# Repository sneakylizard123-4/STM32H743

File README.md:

# STM32H743 FPGA Devboard

> A STM32H743 board with an iCE40 UP5K FPGA, USB High-Speed PHY, Ethernet, and audio I/O.

This board puts an STM32H743XIH6 and an iCE40 UP5K on the same PCB.
The H743 handles control, USB, Ethernet, storage, and audio.
The UP5K provides small programmable logic for custom interfaces and filters, and also an easy way to goof off with the FPGA.
The design is aimed at audio DSP and FPGA experiments that would otherwise need several dev boards.

## Project Status

The board has not been fabricated, assembled, or brought up yet.
Bare-metal firmware is included and builds cleanly, but it has not been run on hardware.
An enclosure and a full mechanical assembly are not included in this revision.

## Custom Features

- STM32H743XIH6, with 2 MB flash and external memory buses exposed on headers.
- iCE40 UP5K FPGA connected to the MCU and to two 2.54 mm headers for logic experiments.
- USB3300 ULPI PHY for USB 2.0 High-Speed, with ESD protection.
- LAN8742A 10/100 Ethernet PHY and an RJ45 jack with integrated magnetics.
- Si5351C clock generator with a 25 MHz TCXO and a 25 MHz crystal. A 32.768 kHz crystal feeds the RTC/LSE on the STM32.
- CS4344 stereo I2S DAC, a 3.5 mm output jack, and two microphones (ICS-43434 and MMICT390200012).
- MicroSD socket on a 4-bit SDMMC bus.
- USB-C sink port for power and USB-A host port with a 500mA power switch.
- Four LDO rails (3.3 V, 2.5 V, 1.8 V, 1.2 V) with ferrite-filtered FPGA supplies.

## How It Works

| Block | Part | Role |
|-------|------|------|
| MCU | STM32H743XIH6 | Main controller, USB, Ethernet MAC, SDMMC, audio, control |
| FPGA | ICE40UP5K-SG48I | Programmable logic and custom interfaces |
| USB PHY | USB3300-EZK | ULPI PHY for USB 2.0 High-Speed |
| Ethernet PHY | LAN8742A | RMII 10/100 PHY |
| Clock | Si5351C-B-GM | Eight-output clock generator |
| Audio DAC | CS4344 | Stereo I2S DAC to the 3.5 mm jack |
| Microphones | ICS-43434, MMICT390200012 | PDM digital microphones |
| Storage | Hirose DM3D-SF | microSD card socket on SDMMC |
| USB power | TPD3S014 | Current-limited USB-A host port switch |
| Power | TLV75733, TLV75725, TLV75718, TLV75712 | 3.3 V, 2.5 V, 1.8 V, and 1.2 V LDO rails |

### Power Tree

```mermaid
flowchart LR
  USB["USB 5 V VBUS"] --> LDO33["U4 TLV75733 3.3 V"]
  USB --> LDO25["U5 TLV75725 2.5 V"]
  USB --> LDO18["U6 TLV75718 1.8 V"]
  USB --> LDO12["U7 TLV75712 1.2 V"]
  LDO33 --> MCU["STM32H743, PHYs, SD, audio"]
  LDO33 --> FB33["Ferrite"] --> FPGA33["3.3VFPGA"]
  LDO25 --> FB25["Ferrite"] --> FPGA25["2.5VFPGA"]
  LDO12 --> FB12["Ferrite"] --> FPGA12["1.2VFPGA"]
  LDO18 --> PHY18["USB3300 VDDA 1.8 V"]
  LDO33 --> PLL["VCCPLL"]
```

The FPGA core, PLL, and I/O rails are separated from the main rails with 1 kohm at 100 MHz ferrites and local decoupling. Each LDO has its own input and output capacitors. The 3.3 V rail also supplies the MCU, Ethernet PHY, audio DAC, microphones, and microSD socket.

## PCB Design

The PCB is 100 x 75.00 mm, 1.6 mm thick, and uses six copper layers. It has two M3 mounting holes. The board has 173 footprints, 966 pads, 2257 track segments, 505 vias, and 6 copper zones.

The 6-layer stackup uses 0.1 mm and 0.535 mm dielectrics with 0.035 mm copper. The FPGA and MCU decoupling is placed on the same side as the pins, and the USB, Ethernet, and SD routes are kept short. Power and ground are distributed on the inner layers.

## Firmware

Bare-metal C firmware is in [firmware](firmware) and is licensed under MIT. It is a self-test and bring-up image, not a full USB, Ethernet, or audio application. It has not been verified on hardware because no board has been assembled yet.

The project uses PlatformIO. Build it with:

```sh
cd firmware
pio run
```

The output is `.pio/build/stm32h743xih6/firmware.elf` and `firmware.bin`. The project pins `ststm32@19.7.0` and uses the custom board definition in `firmware/boards/stm32h743xih6.json`. PlatformIO builds against its `framework-stm32cubeh7` package rather than the vendored `firmware/Drivers` tree, which is kept as reference. The first build may download the platform, framework, and GCC 7.2.1 toolchain.

The checked-in `firmware/src/fpga_bitstream.c` means the FPGA toolchain is only needed when rebuilding the bitstream:

```sh
make -C firmware/fpga
python3 firmware/tools/embed_bitstream.py
```

The firmware uses ARM semihosting over SWD for its console. There is no UART header on rev A, so output only appears while a debugger is attached and the debug enable bit is set. Program the board over SWD with an ST-Link (the default `upload_protocol`) or a J-Link after changing `upload_protocol` and `debug_tool`; there is no USB bootloader or DFU path.

```sh
pio run -t upload   # first upload downloads PlatformIO's OpenOCD package
pio debug           # starts GDB and enables semihosting
```

At boot the firmware configures the 400 MHz clock tree and the three switched LDO rail enables (3.3 V is always on), then runs these checks:

1. Si5351C over I2C and all eight clock outputs.
2. iCE40 bitstream load over SPI1, with CDONE/CRESET handshaking.
3. SDMMC1 card init, CID/CSD read, and a 4-bit bus attempt. The PD4 card-detect pin is not used by the firmware.
4. A short 1 kHz stereo tone through the CS4344 DAC.
5. A LAN8742A MDIO probe and a USB3300 ULPI register probe.
6. A 1 Hz heartbeat on `MCU_ACT`, with `FPGA_ACT` toggling alongside it.

`MCU_FAULT` and `FPGA_FAULT` latch if the Si5351 or FPGA load fails. A missing SD card, PHY, or ULPI device is reported but does not latch a fault. The MIC path is deliberately skipped; see Known Issues.

## Usage

Power the board from the USB-C port. The USB-A port is a host port and is protected by a TPD3S014 load switch and USBLC6 ESD diodes. The USB3300 ULPI PHY is probed in firmware, but no USB device or host stack is implemented.

- Program and debug over SWD.
- Connect Ethernet to the RJ45 jack. The PHY can be probed over MDIO, but the H743 RMII reference clock is not wired, so the Ethernet MAC is not usable in rev A.
- Insert a microSD card in J4. The card uses the 4-bit SDMMC bus.
- Audio output is on J5, the 3.5 mm jack. The two microphones are on the board, but the firmware does not capture from them.
- Some features were left unconnected due to lack of board space

| Interface | Signals on the headers |
|-----------|------------------------|
| FPGA | BANK0_IOT, BANK1_IOB, BANK2_IOB, CDONE, CRESET |
| MCU GPIO | PB, PF, PG, PH, PI, PJ, PK pins |
| Analog | ADC1, ADC2, ADC3, COMP2, OPAMP2 |
| Camera | DCMI D0-D7, HSYNC, VSYNC, PIXCLK |
| Serial | USART1, USART2, USART3, USART6, LPUART1 |
| Other | FDCAN1, I2C2, I2S2, QUADSPI, RTC, SAI1A, SPI4, SWD |

See [kicad/gpio.kicad_sch](kicad/gpio.kicad_sch) for J7 and J8, and [kicad/connector.kicad_sch](kicad/connector.kicad_sch) for J6 and J9. The schematic PDFs and PNG exports are in [images/schematic](images/schematic).

## BOM (Bill of Materials)

Prices were checked on 2026-10-25 at quantity 1. The PCB and shipping lines are estimates. Assembly fees, stencils, taxes, and import charges are not included.

| Item | Cost |
|------|------|
| PCB (qty 5, 6-layer, estimate) | $57.00 |
| Components (one board) | $67.12 |
| Shipping (estimate) | $18.00 |
| **Total** | **$142.12** |

See [BOM.csv](BOM.csv) for the full part list with supplier links and a total cost line.

## Production

The fabrication files are in [kicad/production/STM32H743.zip](kicad/production/STM32H743.zip). The folder contains Gerbers, plated and non-plated drill files, board outline, paste, silkscreen, and solder mask layers. The KiCad source files are in [kicad](kicad).

The board is a 6-layer, 1.6 mm design. For fabrication, use the cheapest standard finish and global standard direct-line shipping.

## Repository Structure

```text
STM32H743/
|-- kicad/                 # KiCad project and 13 hierarchical sheets
|   |-- production/        # Gerbers, drill files, BOM, positions
|   |-- STM32H743.kicad_pro
|   |-- STM32H743.kicad_sch
|   `-- STM32H743.kicad_pcb
|-- cad/
|   `-- STM32H743.step     # STEP export of the PCB assembly
|-- firmware/
|   |-- src/               # Bare-metal C sources and embedded bitstream
|   |-- inc/               # Board, clock, and peripheral headers
|   |-- fpga/              # iCE40 Verilog, constraints, and bitstream Makefile
|   |-- boards/            # PlatformIO custom STM32H743XIH6 board
|   |-- tools/             # Bitstream embedding and PlatformIO helper scripts
|   |-- Drivers/           # Vendored STM32Cube HAL/CMSIS reference tree
|   `-- platformio.ini     # PlatformIO build and upload configuration
|-- blender/
|   `-- STM32H743XIH6.blend
|-- images/
|   |-- render-top.png
|   |-- render-bottom.png
|   |-- pcb.png
|   |-- schematic/         # 14 schematic pages
|   |-- schematic-svg/     # SVG source for the schematic pages
|   `-- screenshots/       # Timestamped progress screenshots
|-- parts/                 # Extra symbols and footprints
|-- BOM.csv
|-- JOURNAL.md
|-- LICENSE                # CERN-OHL-P-2.0 for hardware
|-- LICENSE-MIT            # MIT for firmware
`-- README.md
```

## Known Issues

These are the open items before this board can be treated as a finished product.

1. The LTDC sheet is a placeholder. It has bus labels and notes but no display connector, so the LTDC peripheral is not physically brought out.
2. X2 is a 32.768 kHz LSE crystal on a 3225 4-pad footprint. Common 32.768 kHz crystals are 3215 2-pad. Rev B must change the footprint to 3215 2-pad or use a 4-pad part from a non-LCSC source.
3. C1 is specified as 120 uF in an 0603 footprint, which cannot be assembled. The BOM lists a 47 uF 0603 part instead. This is below the USB 2.0 host recommendation of 120 uF.
4. The ICE40UP5K-SG48ITR is obsolete. The BOM uses the ICE40UP5K-SG48I, which has the same package and an industrial temperature range.
5. Firmware is included but has never run on hardware because no board has been fabricated. Its clock, Si5351, FPGA, SD, audio, Ethernet, and ULPI paths are unverified.
6. Ethernet is not usable in rev A. The LAN8742A is wired for RMII, but the 50 MHz REF_CLK is not connected to the H743 `PA1` pin, which is used for the PHY interrupt instead. The firmware only probes the PHY over MDIO. (Should be fixed as RMII_INT and RMII_REFCLKO share the same pin)
7. No USB stack is included. The USB3300 ULPI PHY is only probed at the register level.
8. The two PDM microphones are not supported by the firmware. MIC1 is wired to `DFSDM1_CKIN1`/`DATIN1`, but its PDM clock is not driven by a clock output, and the SAI2A path to the other microphone would need software PDM decimation.
9. There is no enclosure, no native CAD source, and no mechanical assembly with screws or clips. Only a STEP export of the PCB exists.
10. The design has not been sanity-checked by another person yet.
11. `kicad/fpgaperipherals.kicad_sch` contains three parts that are not on the PCB, and `kicad/sensors.kicad_sch` is empty. Neither sheet is in the hierarchy.
12. The root schematic title block is empty. Add the project title, revision, and author before release.

## Credits and Inspiration

- KiCad symbol, footprint, and 3D model libraries.
- The Hack Club Forge submission checklist and README structure.
- USB3300, LAN8742A, and CS4344 reference schematics from their datasheets.

## License

Hardware design files (schematics, PCB layout, CAD, and images) are licensed under CERN-OHL-P-2.0. See [LICENSE](LICENSE).

SPDX-License-Identifier: CERN-OHL-P-2.0

Firmware is licensed under the MIT License. See [LICENSE-MIT](LICENSE-MIT).

SPDX-License-Identifier: MIT

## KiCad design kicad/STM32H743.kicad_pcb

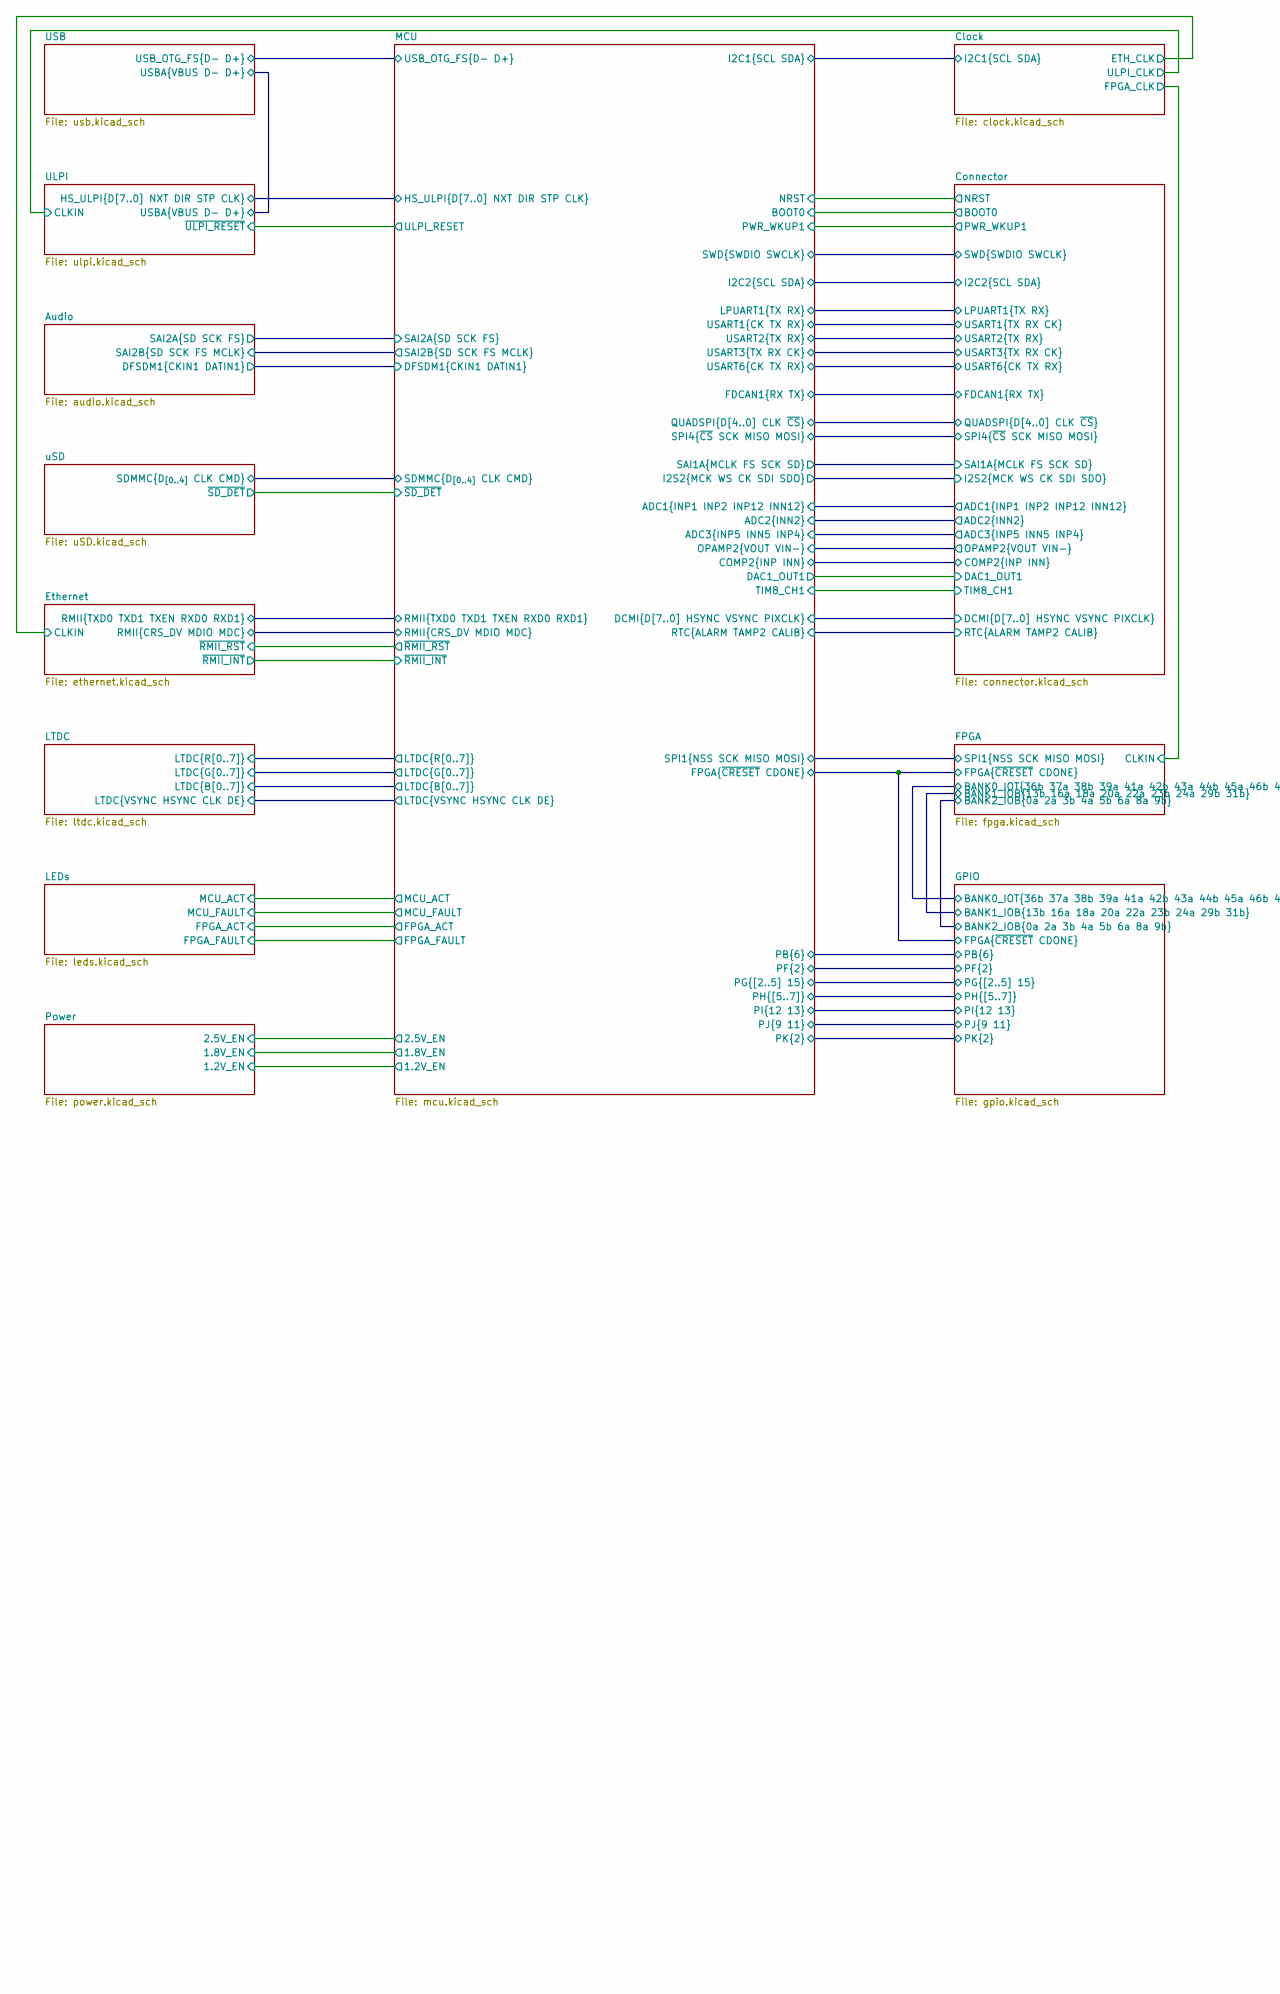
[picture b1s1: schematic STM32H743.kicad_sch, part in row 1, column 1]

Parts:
H1, H2: MountingHole; MountingHole_3.2mm_M3

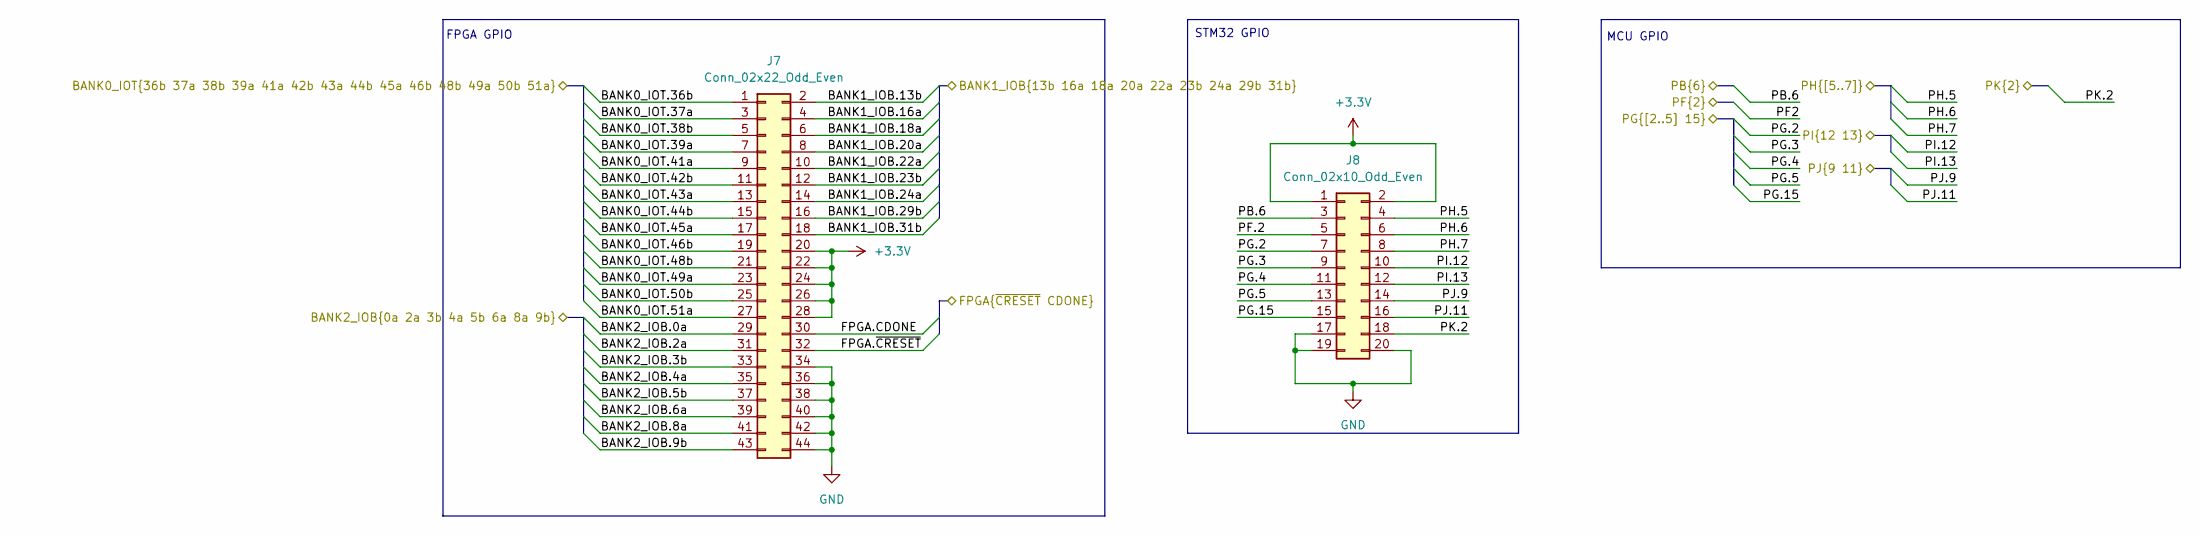
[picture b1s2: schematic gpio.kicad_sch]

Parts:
J7: Conn_02x22_Odd_Even; PinSocket_2x22_P2.54mm_Vertical
J8: Conn_02x10_Odd_Even; PinSocket_2x10_P2.54mm_Vertical

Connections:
+3.3V: J7.20, J7.22, J7.24, J7.26, J7.28, J8.1, J8.2; also elsewhere on the board
/FPGA/BANK0_IOT.36b: J7.1; also elsewhere on the board
/FPGA/BANK0_IOT.37a: J7.3; also elsewhere on the board
/FPGA/BANK0_IOT.38b: J7.5; also elsewhere on the board
/FPGA/BANK0_IOT.39a: J7.7; also elsewhere on the board
/FPGA/BANK0_IOT.41a: J7.9; also elsewhere on the board
/FPGA/BANK0_IOT.42b: J7.11; also elsewhere on the board
/FPGA/BANK0_IOT.43a: J7.13; also elsewhere on the board
/FPGA/BANK0_IOT.44b: J7.15; also elsewhere on the board
/FPGA/BANK0_IOT.45a: J7.17; also elsewhere on the board
/FPGA/BANK0_IOT.46b: J7.19; also elsewhere on the board
/FPGA/BANK0_IOT.48b: J7.21; also elsewhere on the board
/FPGA/BANK0_IOT.49a: J7.23; also elsewhere on the board
/FPGA/BANK0_IOT.50b: J7.25; also elsewhere on the board
/FPGA/BANK0_IOT.51a: J7.27; also elsewhere on the board
/FPGA/BANK1_IOB.13b: J7.2; also elsewhere on the board
/FPGA/BANK1_IOB.16a: J7.4; also elsewhere on the board
/FPGA/BANK1_IOB.18a: J7.6; also elsewhere on the board
/FPGA/BANK1_IOB.20a: J7.8; also elsewhere on the board
/FPGA/BANK1_IOB.22a: J7.10; also elsewhere on the board
/FPGA/BANK1_IOB.23b: J7.12; also elsewhere on the board
/FPGA/BANK1_IOB.24a: J7.14; also elsewhere on the board
/FPGA/BANK1_IOB.29b: J7.16; also elsewhere on the board
/FPGA/BANK1_IOB.31b: J7.18; also elsewhere on the board
/FPGA/BANK2_IOB.0a: J7.29; also elsewhere on the board
/FPGA/BANK2_IOB.2a: J7.31; also elsewhere on the board
/FPGA/BANK2_IOB.3b: J7.33; also elsewhere on the board
/FPGA/BANK2_IOB.4a: J7.35; also elsewhere on the board
/FPGA/BANK2_IOB.5b: J7.37; also elsewhere on the board
/FPGA/BANK2_IOB.6a: J7.39; also elsewhere on the board
/FPGA/BANK2_IOB.8a: J7.41; also elsewhere on the board
/FPGA/BANK2_IOB.9b: J7.43; also elsewhere on the board
/FPGA/FPGA.CDONE: J7.30; also elsewhere on the board
/FPGA/FPGA.~CRESET: J7.32; also elsewhere on the board
/GPIO/PB.6: J8.3; also elsewhere on the board
/GPIO/PF.2: J8.5; also elsewhere on the board
/GPIO/PG.2: J8.7; also elsewhere on the board
/GPIO/PG.3: J8.9; also elsewhere on the board
/GPIO/PG.4: J8.11; also elsewhere on the board
/GPIO/PG.5: J8.13; also elsewhere on the board
/GPIO/PG.15: J8.15; also elsewhere on the board
/GPIO/PH.5: J8.4; also elsewhere on the board
/GPIO/PH.6: J8.6; also elsewhere on the board
/GPIO/PH.7: J8.8; also elsewhere on the board
/GPIO/PI.12: J8.10; also elsewhere on the board
/GPIO/PI.13: J8.12; also elsewhere on the board
/GPIO/PJ.9: J8.14; also elsewhere on the board
/GPIO/PJ.11: J8.16; also elsewhere on the board
/GPIO/PK.2: J8.18; also elsewhere on the board
GND: J7.34, J7.36, J7.38, J7.40, J7.42, J7.44, J8.17, J8.19, J8.20; also elsewhere on the board

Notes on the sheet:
MCU GPIO
FPGA GPIO
STM32 GPIO

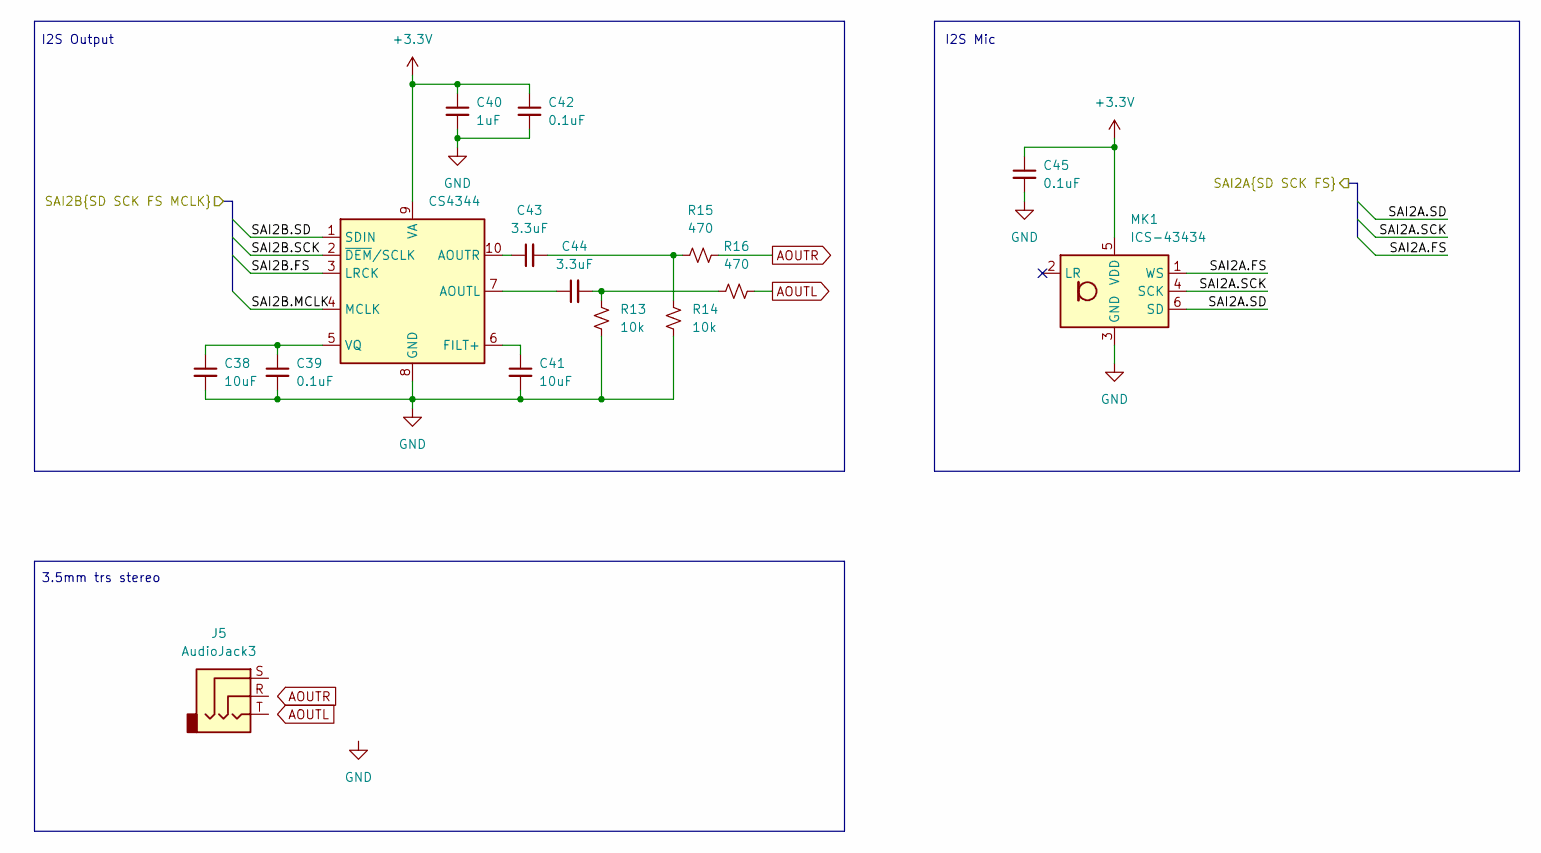
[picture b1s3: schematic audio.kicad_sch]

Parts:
C38, C41: 10uF; C_0603_1608Metric
C39, C42, C45: 0.1uF; C_0603_1608Metric
C40: 1uF; C_0603_1608Metric
C43, C44: 3.3uF; C_0603_1608Metric
J5: AudioJack3; Jack_3.5mm_CUI_SJ-3523-SMT_Horizontal
MK1: ICS-43434; InvenSense_ICS-43434-6_3.5x2.65mm
R13, R14: 10k; R_0603_1608Metric
R15, R16: 470; R_0603_1608Metric
U9: CS4344; TSSOP-10_3x3mm_P0.5mm

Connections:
+3.3V: C40.1, C42.1, C45.1, MK1.5 (VDD), U9.9 (VA); also elsewhere on the board
/Audio/SAI2A.FS: MK1.1 (WS); also elsewhere on the board
/Audio/SAI2A.SCK: MK1.4 (SCK); also elsewhere on the board
/Audio/SAI2A.SD: MK1.6 (SD); also elsewhere on the board
/Audio/SAI2B.FS: U9.3 (LRCK); also elsewhere on the board
/Audio/SAI2B.MCLK: U9.4 (MCLK); also elsewhere on the board
/Audio/SAI2B.SCK: U9.2 (~DEM/SCLK); also elsewhere on the board
/Audio/SAI2B.SD: U9.1 (SDIN); also elsewhere on the board
AOUTL: J5.T, R16.2
AOUTR: J5.R, R15.2
GND: C38.2, C39.2, C40.2, C41.2, C42.2, C45.2, J5.S, MK1.3 (GND), R13.2, R14.2, U9.8 (GND); also elsewhere on the board
unnamed: C43.2, R14.1, R15.1
unnamed: C44.2, R13.1, R16.1
unnamed: C44.1, U9.7 (AOUTL)
unnamed: C43.1, U9.10 (AOUTR)
unnamed: C41.1, U9.6 (FILT+)
unnamed: C38.1, C39.1, U9.5 (VQ)

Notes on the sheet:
I2S Output
3.5mm trs stereo
I2S Mic

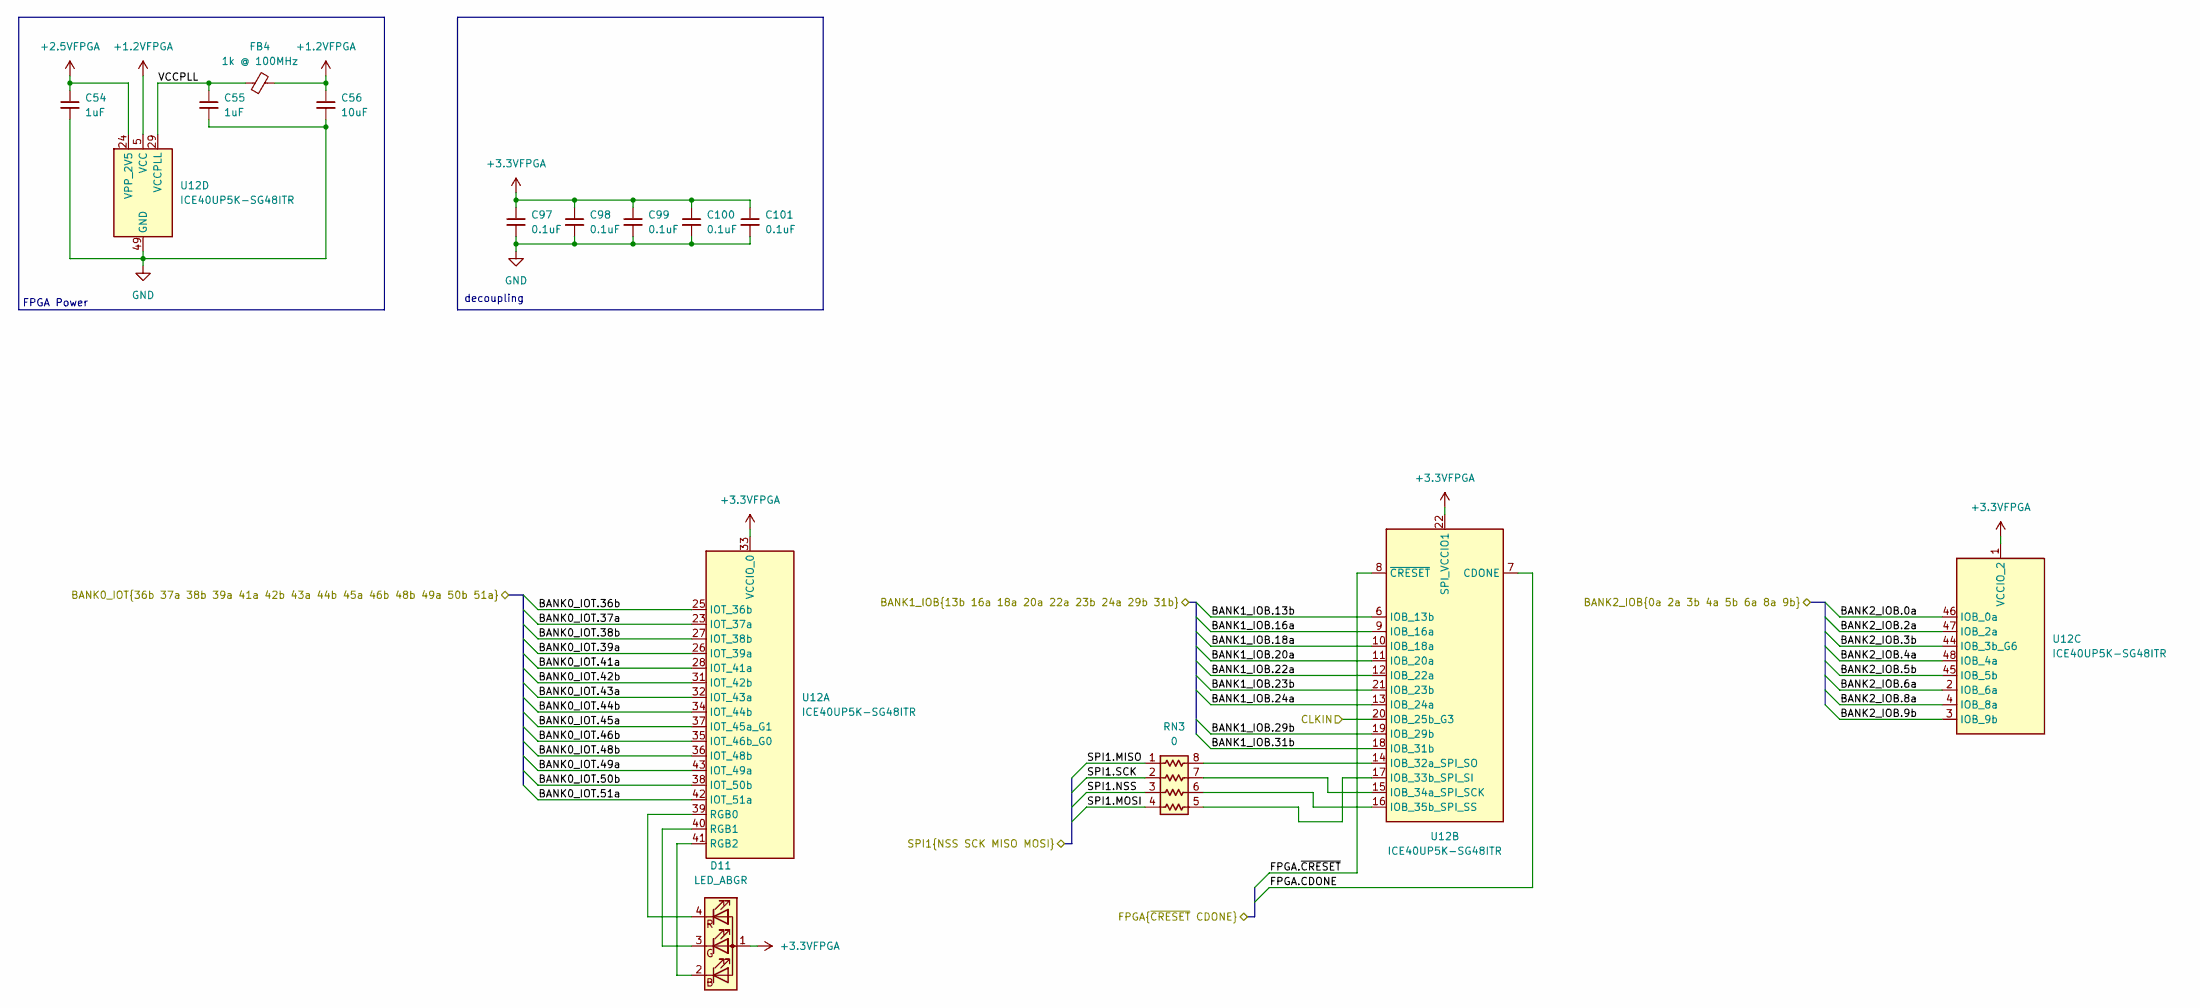
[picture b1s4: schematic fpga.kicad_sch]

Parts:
C54, C55: 1uF; C_0603_1608Metric
C56: 10uF; C_0603_1608Metric
C97, C98, C99, C100, C101: 0.1uF; C_0603_1608Metric
D11: LED_ABGR; LED_Cree-PLCC4_2x2mm_CW; LCSC C5620247
FB4: 1k @ 100MHz; Ferrite_0603_1608Metric
RN3: 0; R_Array_Concave_4x0603
U12: ICE40UP5K-SG48ITR; QFN-48-1EP_7x7mm_P0.5mm_EP5.6x5.6mm

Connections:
+1.2VFPGA: C56.1, FB4.2, U12.5 (VCC), U12.30 (VCC); also elsewhere on the board
+2.5VFPGA: C54.1, U12.24 (VPP_2V5); also elsewhere on the board
+3.3VFPGA: C97.1, C98.1, C99.1, C100.1, C101.1, D11.1 (A), U12.1 (VCCIO_2), U12.22 (SPI_VCCIO1), U12.33 (VCCIO_0); also elsewhere on the board
/Clock/FPGA_CLK: U12.20 (IOB_25b_G3); also elsewhere on the board
/FPGA/BANK0_IOT.36b: U12.25 (IOT_36b); also elsewhere on the board
/FPGA/BANK0_IOT.37a: U12.23 (IOT_37a); also elsewhere on the board
/FPGA/BANK0_IOT.38b: U12.27 (IOT_38b); also elsewhere on the board
/FPGA/BANK0_IOT.39a: U12.26 (IOT_39a); also elsewhere on the board
/FPGA/BANK0_IOT.41a: U12.28 (IOT_41a); also elsewhere on the board
/FPGA/BANK0_IOT.42b: U12.31 (IOT_42b); also elsewhere on the board
/FPGA/BANK0_IOT.43a: U12.32 (IOT_43a); also elsewhere on the board
/FPGA/BANK0_IOT.44b: U12.34 (IOT_44b); also elsewhere on the board
/FPGA/BANK0_IOT.45a: U12.37 (IOT_45a_G1); also elsewhere on the board
/FPGA/BANK0_IOT.46b: U12.35 (IOT_46b_G0); also elsewhere on the board
/FPGA/BANK0_IOT.48b: U12.36 (IOT_48b); also elsewhere on the board
/FPGA/BANK0_IOT.49a: U12.43 (IOT_49a); also elsewhere on the board
/FPGA/BANK0_IOT.50b: U12.38 (IOT_50b); also elsewhere on the board
/FPGA/BANK0_IOT.51a: U12.42 (IOT_51a); also elsewhere on the board
/FPGA/BANK1_IOB.13b: U12.6 (IOB_13b); also elsewhere on the board
/FPGA/BANK1_IOB.16a: U12.9 (IOB_16a); also elsewhere on the board
/FPGA/BANK1_IOB.18a: U12.10 (IOB_18a); also elsewhere on the board
/FPGA/BANK1_IOB.20a: U12.11 (IOB_20a); also elsewhere on the board
/FPGA/BANK1_IOB.22a: U12.12 (IOB_22a); also elsewhere on the board
/FPGA/BANK1_IOB.23b: U12.21 (IOB_23b); also elsewhere on the board
/FPGA/BANK1_IOB.24a: U12.13 (IOB_24a); also elsewhere on the board
/FPGA/BANK1_IOB.29b: U12.19 (IOB_29b); also elsewhere on the board
/FPGA/BANK1_IOB.31b: U12.18 (IOB_31b); also elsewhere on the board
/FPGA/BANK2_IOB.0a: U12.46 (IOB_0a); also elsewhere on the board
/FPGA/BANK2_IOB.2a: U12.47 (IOB_2a); also elsewhere on the board
/FPGA/BANK2_IOB.3b: U12.44 (IOB_3b_G6); also elsewhere on the board
/FPGA/BANK2_IOB.4a: U12.48 (IOB_4a); also elsewhere on the board
/FPGA/BANK2_IOB.5b: U12.45 (IOB_5b); also elsewhere on the board
/FPGA/BANK2_IOB.6a: U12.2 (IOB_6a); also elsewhere on the board
/FPGA/BANK2_IOB.8a: U12.4 (IOB_8a); also elsewhere on the board
/FPGA/BANK2_IOB.9b: U12.3 (IOB_9b); also elsewhere on the board
/FPGA/FPGA.CDONE: U12.7 (CDONE); also elsewhere on the board
/FPGA/FPGA.~CRESET: U12.8 (~CRESET); also elsewhere on the board
/FPGA/SPI1.MISO: RN3.1 (R1.1); also elsewhere on the board
/FPGA/SPI1.MOSI: RN3.4 (R4.1); also elsewhere on the board
/FPGA/SPI1.NSS: RN3.3 (R3.1); also elsewhere on the board
/FPGA/SPI1.SCK: RN3.2 (R2.1); also elsewhere on the board
/FPGA/VCCPLL: C55.1, FB4.1, U12.29 (VCCPLL)
GND: C54.2, C55.2, C56.2, C97.2, C98.2, C99.2, C100.2, C101.2, U12.49 (GND); also elsewhere on the board
unnamed: D11.2 (BK), U12.41 (RGB2)
unnamed: D11.3 (GK), U12.40 (RGB1)
unnamed: D11.4 (RK), U12.39 (RGB0)
unnamed: RN3.8 (R1.2), U12.14 (IOB_32a_SPI_SO)
unnamed: RN3.7 (R2.2), U12.15 (IOB_34a_SPI_SCK)
unnamed: RN3.6 (R3.2), U12.16 (IOB_35b_SPI_SS)
unnamed: RN3.5 (R4.2), U12.17 (IOB_33b_SPI_SI)

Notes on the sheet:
decoupling
FPGA Power

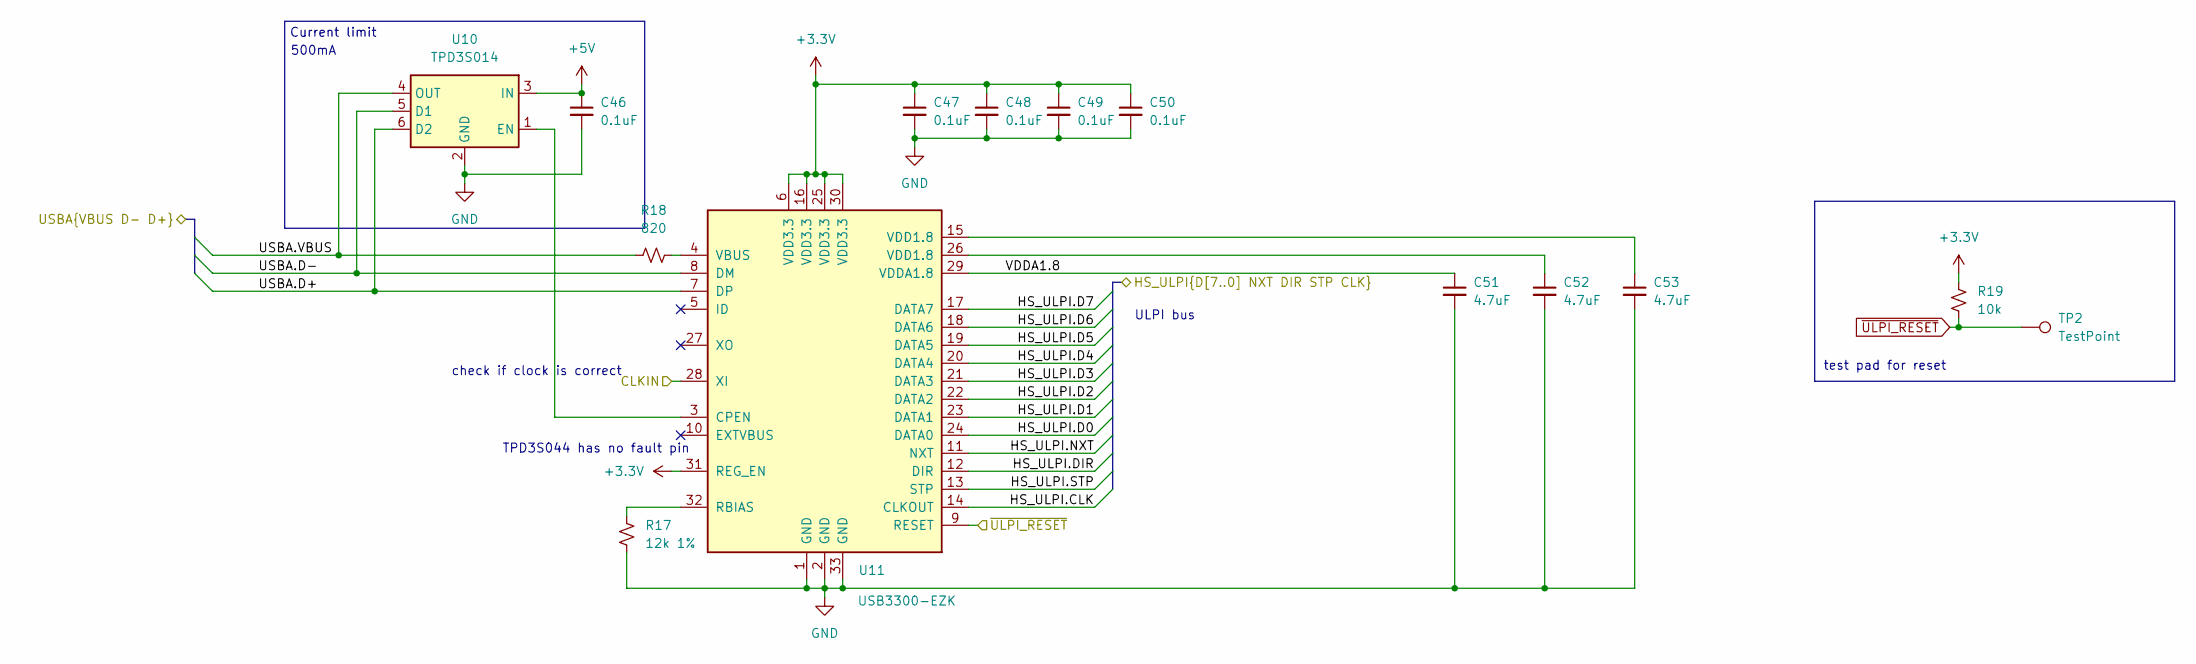
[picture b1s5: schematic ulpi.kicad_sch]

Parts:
C46, C47, C48, C49, C50: 0.1uF; C_0603_1608Metric
C51, C52, C53: 4.7uF; C_0603_1608Metric
R17: 12k 1%; R_0603_1608Metric
R18: 820; R_0603_1608Metric
R19: 10k; R_0603_1608Metric
TP2: TestPoint; TestPoint_Pad_D1.5mm
U10: TPD3S014; SOT-23-6
U11: USB3300-EZK; QFN-32-1EP_5x5mm_P0.5mm_EP3.45x3.45mm

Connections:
+3.3V: C47.1, C48.1, C49.1, C50.1, R19.1, U11.6 (VDD3.3), U11.16 (VDD3.3), U11.25 (VDD3.3), U11.30 (VDD3.3), U11.31 (REG_EN); also elsewhere on the board
+5V: C46.1, U10.3 (IN); also elsewhere on the board
/Clock/ULPI_CLK: U11.28 (XI); also elsewhere on the board
/MCU/HS_ULPI.CLK: U11.14 (CLKOUT); also elsewhere on the board
/MCU/HS_ULPI.D0: U11.24 (DATA0); also elsewhere on the board
/MCU/HS_ULPI.D1: U11.23 (DATA1); also elsewhere on the board
/MCU/HS_ULPI.D2: U11.22 (DATA2); also elsewhere on the board
/MCU/HS_ULPI.D3: U11.21 (DATA3); also elsewhere on the board
/MCU/HS_ULPI.D4: U11.20 (DATA4); also elsewhere on the board
/MCU/HS_ULPI.D5: U11.19 (DATA5); also elsewhere on the board
/MCU/HS_ULPI.D6: U11.18 (DATA6); also elsewhere on the board
/MCU/HS_ULPI.D7: U11.17 (DATA7); also elsewhere on the board
/MCU/HS_ULPI.DIR: U11.12 (DIR); also elsewhere on the board
/MCU/HS_ULPI.NXT: U11.11 (NXT); also elsewhere on the board
/MCU/HS_ULPI.STP: U11.13 (STP); also elsewhere on the board
/ULPI/USBA.D+: U10.6 (D2), U11.7 (DP); also elsewhere on the board
/ULPI/USBA.D-: U10.5 (D1), U11.8 (DM); also elsewhere on the board
/ULPI/USBA.VBUS: R18.1, U10.4 (OUT); also elsewhere on the board
/ULPI/VDDA1.8: C51.1, U11.29 (VDDA1.8)
GND: C46.2, C47.2, C48.2, C49.2, C50.2, C51.2, C52.2, C53.2, R17.2, U10.2 (GND), U11.1 (GND), U11.2 (GND), U11.33 (GND); also elsewhere on the board
unnamed: C52.1, U11.26 (VDD1.8)
unnamed: C53.1, U11.15 (VDD1.8)
unnamed: U10.1 (EN), U11.3 (CPEN)
unnamed: R17.1, U11.32 (RBIAS)
unnamed: R18.2, U11.4 (VBUS)
~ULPI_RESET: R19.2, TP2.1 (1_1), U11.9 (RESET); also elsewhere on the board

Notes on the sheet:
Current limit
TPD3S044 has no fault pin
test pad for reset
ULPI bus
500mA
check if clock is correct

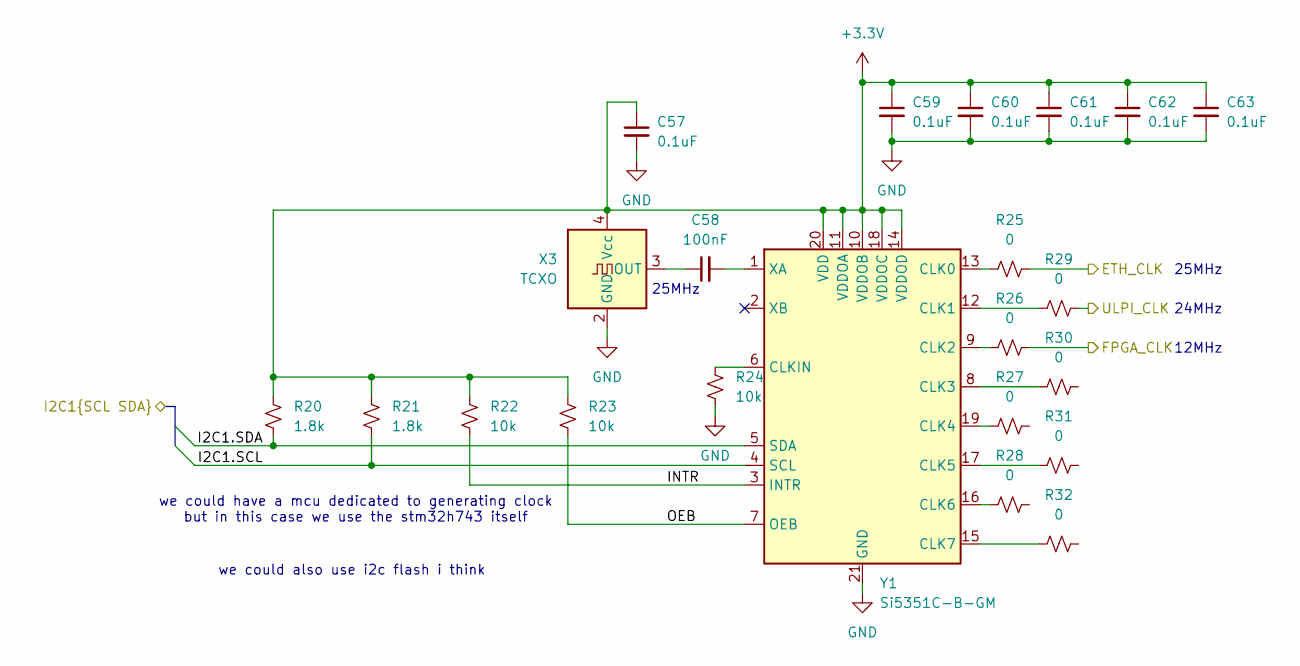
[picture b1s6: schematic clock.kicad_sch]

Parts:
C57, C59, C60, C61, C62, C63: 0.1uF; C_0603_1608Metric
C58: 100nF; C_0603_1608Metric
R20, R21: 1.8k; R_0603_1608Metric
R22, R23, R24: 10k; R_0603_1608Metric
R25, R26, R27, R28, R29, R30, R31, R32: 0; R_0603_1608Metric
X3: TCXO; Oscillator_SMD_SeikoEpson_TG2520SMN-xxx-xxxxxx-4Pin_2.5x2.0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; Part Number 8122S-25.000NQ33FTL
Y1: Si5351C-B-GM; QFN-20-1EP_4x4mm_P0.5mm_EP2.7x2.7mm

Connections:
+3.3V: C57.1, C59.1, C60.1, C61.1, C62.1, C63.1, R20.1, R21.1, R22.1, R23.1, X3.4 (Vcc), Y1.10 (VDDOB), Y1.11 (VDDOA), Y1.14 (VDDOD), Y1.18 (VDDOC), Y1.20 (VDD); also elsewhere on the board
/Clock/ETH_CLK: R25.2; also elsewhere on the board
/Clock/FPGA_CLK: R26.2; also elsewhere on the board
/Clock/I2C1.SCL: R21.2, Y1.4 (SCL); also elsewhere on the board
/Clock/I2C1.SDA: R20.2, Y1.5 (SDA); also elsewhere on the board
/Clock/INTR: R22.2, Y1.3 (INTR)
/Clock/OEB: R23.2, Y1.7 (OEB)
/Clock/ULPI_CLK: R29.2; also elsewhere on the board
GND: C57.2, C59.2, C60.2, C61.2, C62.2, C63.2, R24.2, X3.2 (GND), Y1.21 (GND); also elsewhere on the board
unnamed 251: R27.2; also elsewhere on the board
unnamed 252: R28.2; also elsewhere on the board
unnamed 253: R30.2; also elsewhere on the board
unnamed 254: R31.2; also elsewhere on the board
unnamed 255: R32.2; also elsewhere on the board
unnamed: C58.1, X3.3 (OUT)
unnamed: R25.1, Y1.13 (CLK0)
unnamed: R29.1, Y1.12 (CLK1)
unnamed: R26.1, Y1.9 (CLK2)
unnamed: R30.1, Y1.8 (CLK3)
unnamed: R27.1, Y1.19 (CLK4)
unnamed: R31.1, Y1.17 (CLK5)
unnamed: R28.1, Y1.16 (CLK6)
unnamed: R32.1, Y1.15 (CLK7)
unnamed: R24.1, Y1.6 (CLKIN)
unnamed: C58.2, Y1.1 (XA)

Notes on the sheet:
25MHz
we could also use i2c flash i think
we could have a mcu dedicated to generating clock but in this case we use the stm32h743 itself
24MHz
12MHz
